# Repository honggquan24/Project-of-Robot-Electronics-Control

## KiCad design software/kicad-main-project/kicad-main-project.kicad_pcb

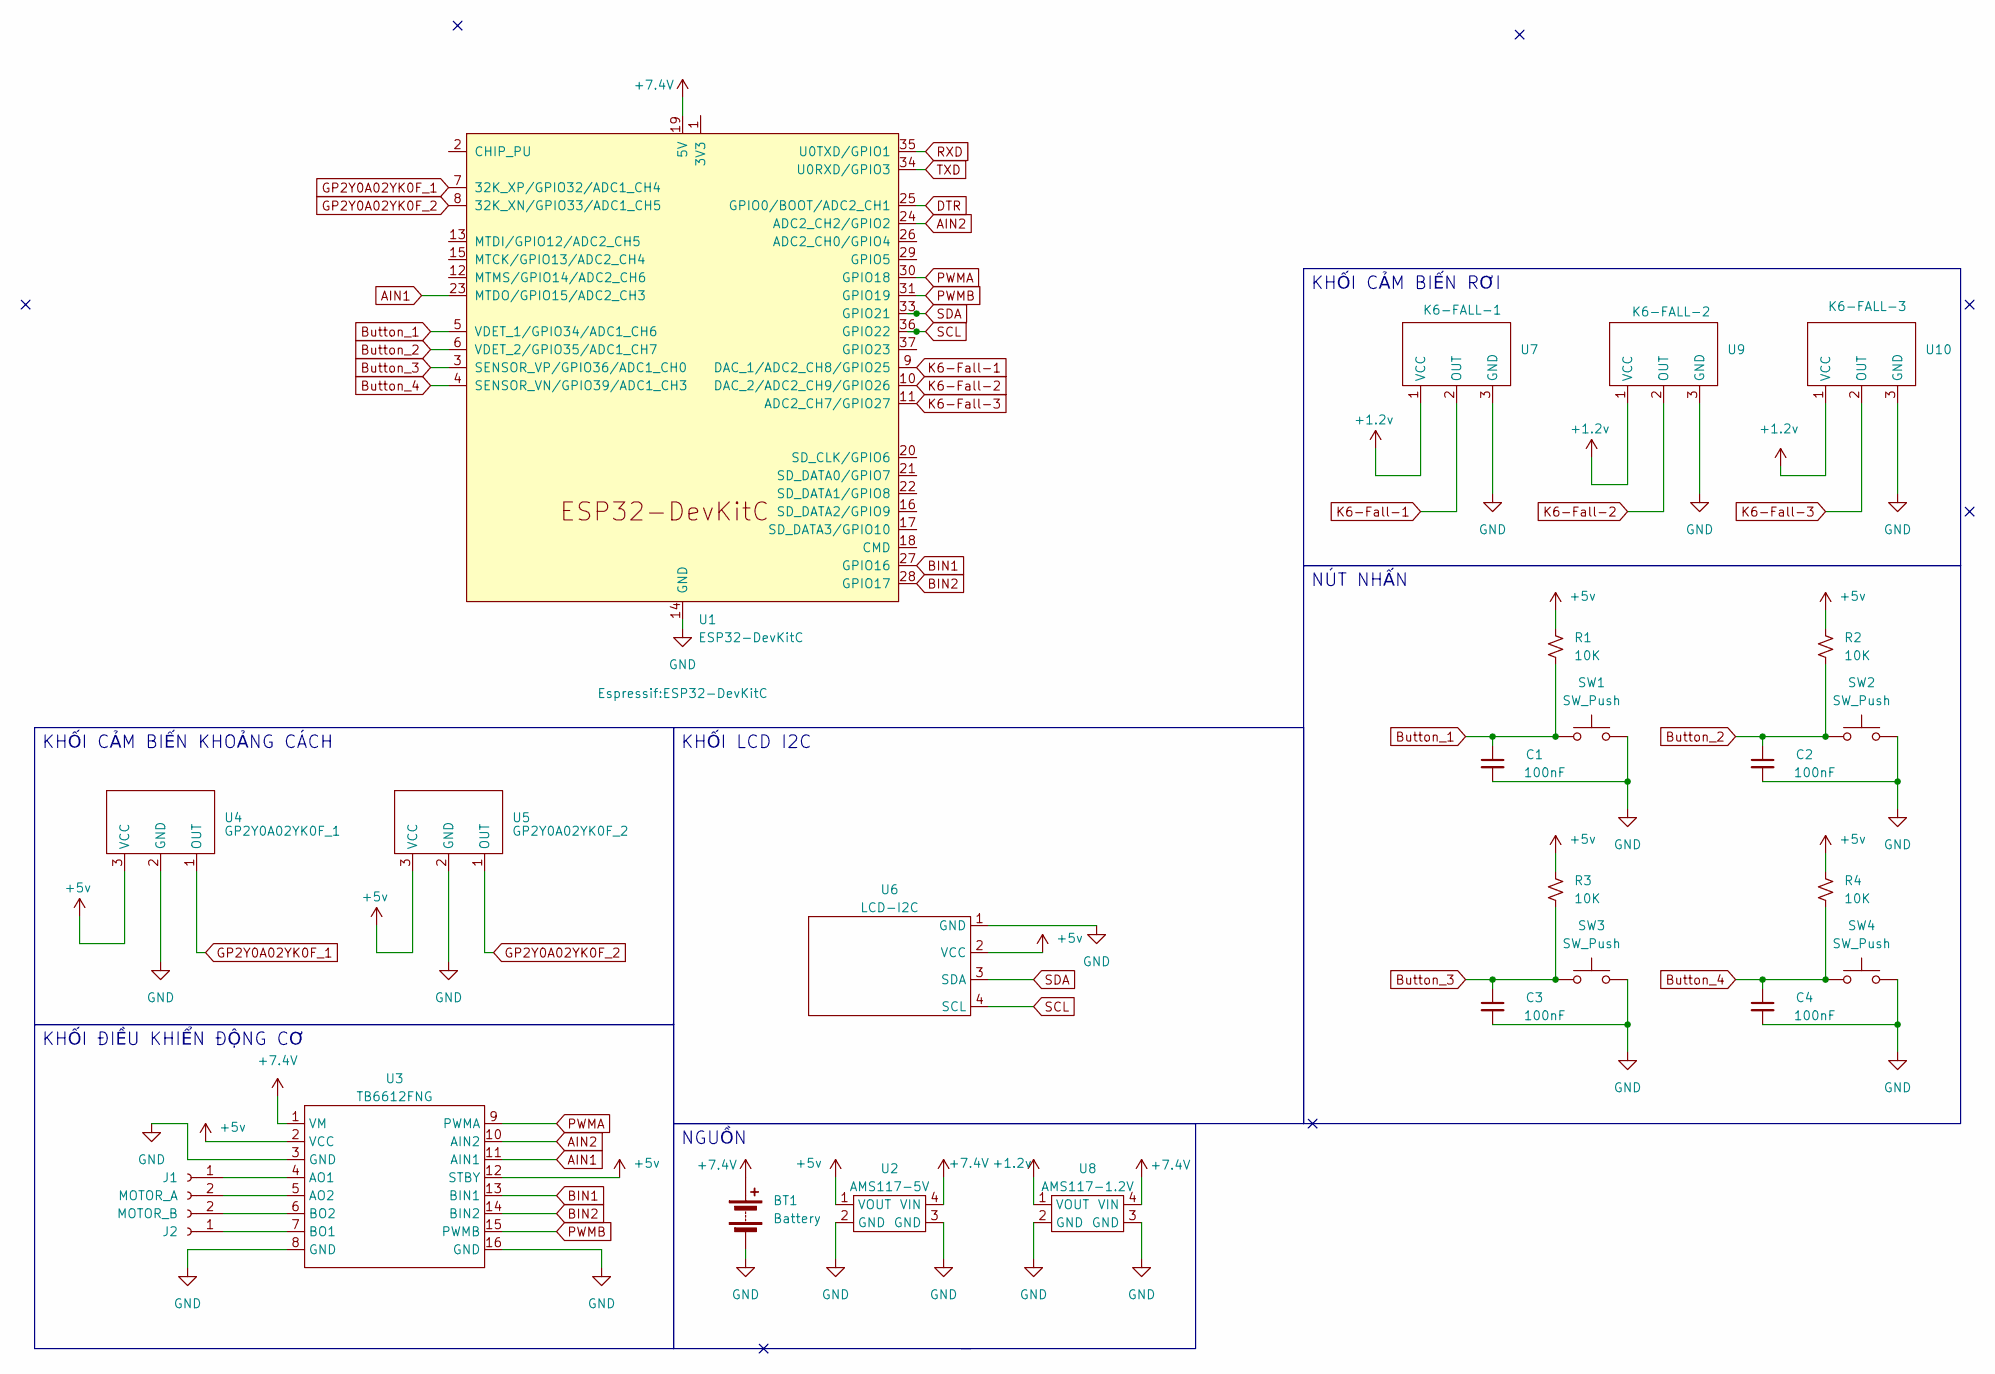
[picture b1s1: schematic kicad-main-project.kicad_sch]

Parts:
BT1: Battery; JST_XH_S2B-XH-A-1_1x02_P2.50mm_Horizontal
C1, C2, C3, C4: 100nF; C_Disc_D3.0mm_W1.6mm_P2.50mm
J1: MOTOR_A; JST_XH_S2B-XH-A-1_1x02_P2.50mm_Horizontal
J2: MOTOR_B; JST_XH_S2B-XH-A-1_1x02_P2.50mm_Horizontal
R1, R2, R3, R4: 10K; R_Axial_DIN0204_L3.6mm_D1.6mm_P2.54mm_Vertical
SW1, SW2, SW3, SW4: SW_Push; SW_PUSH-12mm
U1: ESP32-DevKitC
U2: AMS117-5V; Untitled
U3: TB6612FNG; Untitled
U4: GP2Y0A02YK0F_1; JST_XH_S3B-XH-A-1_1x03_P2.50mm_Horizontal
U5: GP2Y0A02YK0F_2; JST_XH_S3B-XH-A-1_1x03_P2.50mm_Horizontal
U6: LCD-I2C; JST_XH_S4B-XH-A_1x04_P2.50mm_Horizontal
U7: K6-FALL-1; JST_XH_S3B-XH-A-1_1x03_P2.50mm_Horizontal
U8: AMS117-1.2V; Untitled
U9: K6-FALL-2; JST_XH_S3B-XH-A-1_1x03_P2.50mm_Horizontal
U10: K6-FALL-3; JST_XH_S3B-XH-A-1_1x03_P2.50mm_Horizontal

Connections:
+1.2v: U7.1 (VCC), U8.1 (VOUT), U9.1 (VCC), U10.1 (VCC)
+5v: R1.1, R2.1, R3.1, R4.1, U2.1 (VOUT), U3.2 (VCC), U3.12 (STBY), U4.3 (VCC), U5.3 (VCC), U6.2 (VCC)
+7.4V: BT1.1 (+), U1.19 (5V), U2.4 (VIN), U3.1 (VM), U8.4 (VIN)
AIN1: U1.23 (MTDO/GPIO15/ADC2_CH3), U3.11 (AIN1)
AIN2: U1.24 (ADC2_CH2/GPIO2), U3.10 (AIN2)
BIN1: U1.27 (GPIO16), U3.13 (BIN1)
BIN2: U1.28 (GPIO17), U3.14 (BIN2)
Button_1: C1.1, R1.2, SW1.1, U1.5 (VDET_1/GPIO34/ADC1_CH6)
Button_2: C2.1, R2.2, SW2.1, U1.6 (VDET_2/GPIO35/ADC1_CH7)
Button_3: C3.1, R3.2, SW3.1, U1.3 (SENSOR_VP/GPIO36/ADC1_CH0)
Button_4: C4.1, R4.2, SW4.1, U1.4 (SENSOR_VN/GPIO39/ADC1_CH3)
DTR: U1.25 (GPIO0/BOOT/ADC2_CH1)
GND: BT1.2 (-), C1.2, C2.2, C3.2, C4.2, SW1.2, SW2.2, SW3.2, SW4.2, U1.14 (GND), U1.32 (GND), U1.38 (GND), U2.2 (GND), U2.3 (GND), U3.3 (GND), U3.8 (GND), U3.16 (GND), U4.2 (GND), U5.2 (GND), U6.1 (GND), U7.3 (GND), U8.2 (GND), U8.3 (GND), U9.3 (GND), U10.3 (GND)
GP2Y0A02YK0F_1: U1.7 (32K_XP/GPIO32/ADC1_CH4), U4.1 (OUT)
GP2Y0A02YK0F_2: U1.8 (32K_XN/GPIO33/ADC1_CH5), U5.1 (OUT)
K6-Fall-1: U1.9 (DAC_1/ADC2_CH8/GPIO25), U7.2 (OUT)
K6-Fall-2: U1.10 (DAC_2/ADC2_CH9/GPIO26), U9.2 (OUT)
K6-Fall-3: U1.11 (ADC2_CH7/GPIO27), U10.2 (OUT)
unnamed: J1.1, U3.4 (AO1)
unnamed: J1.2, U3.5 (AO2)
unnamed: J2.1, U3.7 (BO1)
unnamed: J2.2, U3.6 (BO2)
PWMA: U1.30 (GPIO18), U3.9 (PWMA)
PWMB: U1.31 (GPIO19), U3.15 (PWMB)
RXD: U1.35 (U0TXD/GPIO1)
SCL: U1.36 (GPIO22), U6.4 (SCL)
SDA: U1.33 (GPIO21), U6.3 (SDA)
TXD: U1.34 (U0RXD/GPIO3)

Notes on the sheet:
KHỐI CẢM BIẾN RƠI
KHỐI LCD I2C
NÚT NHẤN
NGUỒN
KHỐI ĐIỀU KHIỂN ĐỘNG CƠ
KHỐI CẢM BIẾN KHOẢNG CÁCH

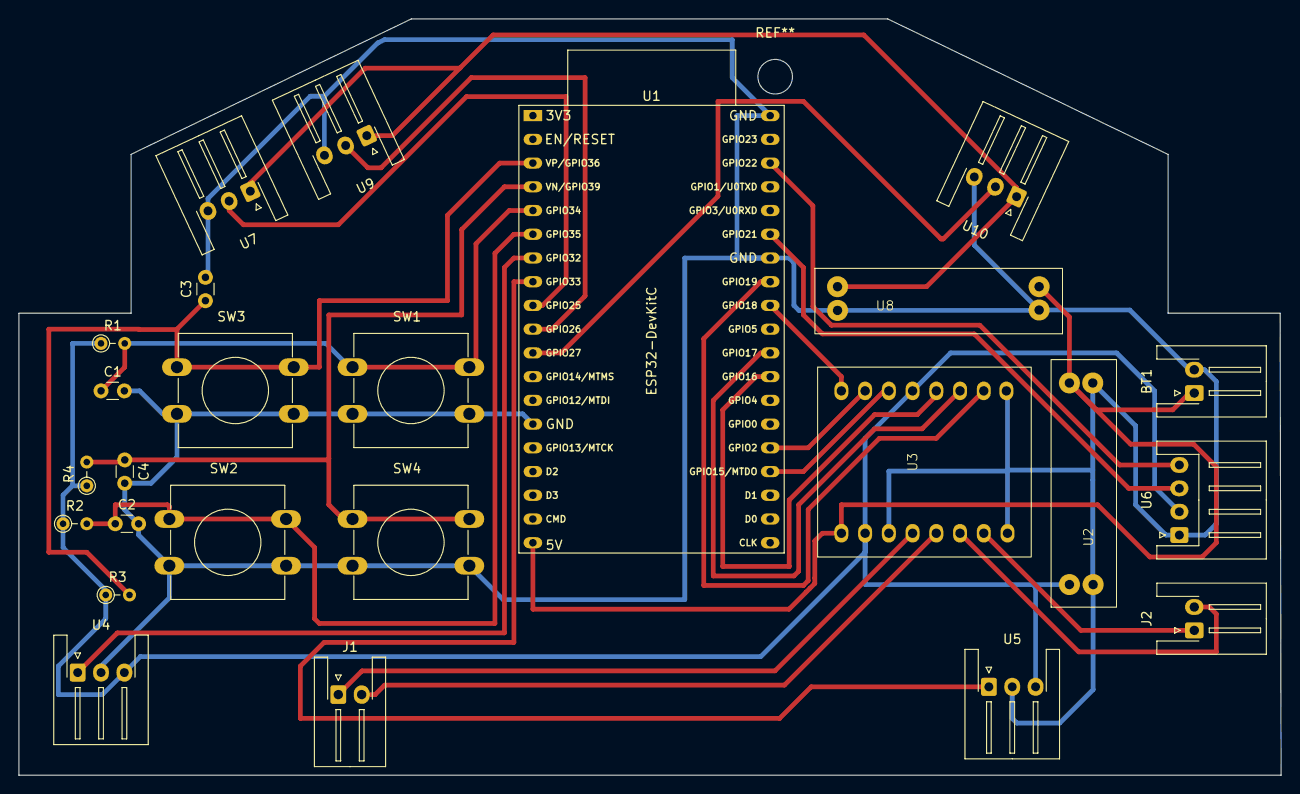
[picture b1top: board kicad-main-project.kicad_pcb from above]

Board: 2 copper layers, 135.1 x 80.9 mm, 25 parts (0 on the bottom side), 25 nets.

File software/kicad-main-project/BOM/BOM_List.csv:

Reference,Qty,Value,DNP,Exclude from BOM,Exclude from Board,Footprint,Datasheet
BT1,1,Battery,,,,Connector_JST:JST_XH_S2B-XH-A-1_1x02_P2.50mm_Horizontal,~
"C1,C2,C3,C4",4,100nF,,,,Capacitor_THT:C_Disc_D3.0mm_W1.6mm_P2.50mm,~
J1,1,MOTOR_A,,,,Connector_JST:JST_XH_S2B-XH-A-1_1x02_P2.50mm_Horizontal,~
J2,1,MOTOR_B,,,,Connector_JST:JST_XH_S2B-XH-A-1_1x02_P2.50mm_Horizontal,~
"R1,R2,R3,R4",4,10K,,,,Resistor_THT:R_Axial_DIN0204_L3.6mm_D1.6mm_P2.54mm_Vertical,~
"SW1,SW2,SW3,SW4",4,SW_Push,,,,Button_Switch_THT:SW_PUSH-12mm,~
U1,1,ESP32-DevKitC,,,,Espressif:ESP32-DevKitC,https://docs.espressif.com/projects/esp-idf/zh_CN/latest/esp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
U2,1,AMS117-5V,,,,myAMS117-5V:Untitled,
U3,1,TB6612FNG,,,,myTB6612FNG:Untitled,
U4,1,GP2Y0A02YK0F_1,,,,Connector_JST:JST_XH_S3B-XH-A-1_1x03_P2.50mm_Horizontal,
U5,1,GP2Y0A02YK0F_2,,,,Connector_JST:JST_XH_S3B-XH-A-1_1x03_P2.50mm_Horizontal,
U6,1,LCD-I2C,,,,Connector_JST:JST_XH_S4B-XH-A_1x04_P2.50mm_Horizontal,
U7,1,K6-FALL-1,,,,Connector_JST:JST_XH_S3B-XH-A-1_1x03_P2.50mm_Horizontal,
U8,1,AMS117-1.2V,,,,myAMS117-5V:Untitled,
U9,1,K6-FALL-2,,,,Connector_JST:JST_XH_S3B-XH-A-1_1x03_P2.50mm_Horizontal,
U10,1,K6-FALL-3,,,,Connector_JST:JST_XH_S3B-XH-A-1_1x03_P2.50mm_Horizontal,

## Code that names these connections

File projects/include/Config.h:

#ifndef CONFIG_H
#define CONFIG_H

#include <Arduino.h>

// U3
const int MOTOR_LEFT_IN1_PIN  = 15;   // AIN1 của U3 
const int MOTOR_LEFT_IN2_PIN  = 2;  // AIN2 của U3 
const int MOTOR_LEFT_PWM_PIN  = 18;  // PWMA của U3 

const int MOTOR_RIGHT_IN1_PIN = 16;   // BIN1 của U3 
const int MOTOR_RIGHT_IN2_PIN = 17;  // BIN2 của U3 
const int MOTOR_RIGHT_PWM_PIN = 19;  // PWMB của U3 

// U4 - U5
const int DISTANCE_SENSOR_RIGHT_PIN = 32;  // U4 OUT (GP2Y0A02YKOF_1)
const int DISTANCE_SENSOR_FRONT_PIN = 33;  // U5 OUT (GP2Y0A02YKOF_2) 

// U6
const int I2C_SDA_PIN = 21; 
const int I2C_SCL_PIN = 22; 

// MOTOR PWM CONFIGURATION ===
const int PWM_FREQ = 5000;
const int PWM_RESOLUTION = 8;
const int PWM_CHANNEL_LEFT = 0;
const int PWM_CHANNEL_RIGHT = 1;

// LCD I2C CONFIGURATION 
const int LCD_COLUMNS = 16;
const int LCD_ROWS = 2;
const uint8_t LCD_I2C_ADDRESS = 0x27; 

enum RobotSystemState { // Đổi tên để tránh trùng với biến `currentState` có thể có ở đâu đó
    STATE_IDLE,
    STATE_WALL_FOLLOWING,
    STATE_OBSTACLE_AVOID_TURN, // Trạng thái chung khi cần rẽ vì vật cản
    STATE_MENU_MAIN,
    STATE_MENU_TUNE_PID,
    STATE_MENU_SETTINGS,
    STATE_EDIT_VALUE
};

extern int g_basePwmSpeed; // Khai báo extern
extern unsigned long g_turnDurationMs; // Khai báo extern

const int BUTTON_MODE_PIN         = 36; // SW1 (Net Switch_1)
const int BUTTON_SELECT_PIN       = 39; // SW2 (Net Switch_2)
const int BUTTON_UP_PIN           = 35; // SW3 (Net Switch_3)
const int BUTTON_DOWN_PIN         = 34; // SW4 (Net Switch_4)


extern const char* const ROBOT_STATE_NAMES[]; // Khai báo extern cho mảng tên trạng thái
extern const int NUM_ROBOT_SYSTEM_STATES;     // Số lượng trạng thái thực tế (không tính UNKNOWN nếu có)

// === WALL FOLLOWING PID CONFIGURATION ===
extern float g_kp; // Các biến toàn cục cho PID, tiền tố g_ để rõ ràng
extern float g_ki;
extern float g_kd;
extern float g_targetDistanceCm; // Setpoint có thể thay đổi

const float SETPOINT_INCREMENT_CM = 1.0f;
const float MIN_TARGET_DISTANCE_CM = 15.0f;
const float MAX_TARGET_DISTANCE_CM = 60.0f;

const int   BASE_PWM_SPEED = 90;
const float PID_OUTPUT_MIN = -70.0f;
const float PID_OUTPUT_MAX = 70.0f;

// === FRONT OBSTACLE AVOIDANCE ===
const float MIN_FRONT_DISTANCE_TO_STOP_CM = 30.0f;
const unsigned long TURN_DURATION_MS = 1400; // Thời gian quay (cần tune)
const int TURN_PWM_SPEED = 100;             // Tốc độ khi quay

// === BUTTON DEBOUNCE ===
const unsigned long DEBOUNCE_DELAY_MS = 50;

// === TIMING ===
const long SERIAL_BAUD_RATE = 115200;
const unsigned long PYTHON_DATA_SEND_INTERVAL_MS = 200;
const unsigned long CONTROL_LOOP_INTERVAL_MS = 20;
const unsigned long LCD_UPDATE_INTERVAL_MS = 250;

#endif // CONFIG_H

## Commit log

2025-04-10 update library
2025-05-04 update schematic
2025-05-05 update pcb
2025-05-10 update gerber + bom + image_
2025-06-18 update báo cáo
